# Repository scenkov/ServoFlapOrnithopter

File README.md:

# ESP32 board and SBUS receiver 
Thanks to K.Kakuta for the enormous work

Arduino CODE for ServoFlapOrnithopter [ServoFlapOrnithopter 2 servo by K.Kakuta](http://kakutaclinic.life.coocan.jp/SFOsys2S.html)

The library uses [ESP32Servo](https://www.arduino.cc/reference/en/libraries/esp32servo/) Allows ESP32 boards to control servo, tone and analogWrite motors using Arduino semantics.
This library can control a many types of servos. It makes use of the ESP32 PWM timers: the library can control up to 16 servos on individual channels No attempt has been made to support multiple servos per channel. 

### Installation
Download the contents of this repository on your computer. Open with PlatformIO

## Usage

Schematic 

Board 

New Servo Flap System by K.Kakuta

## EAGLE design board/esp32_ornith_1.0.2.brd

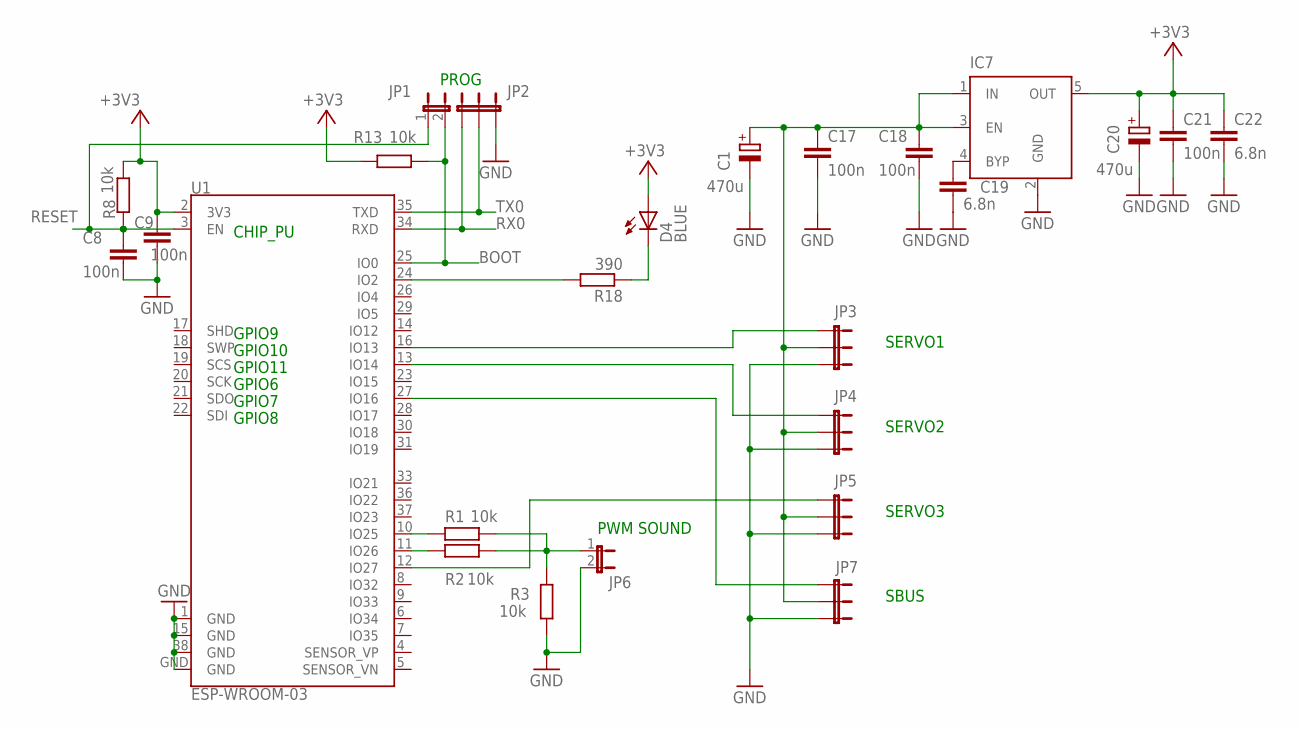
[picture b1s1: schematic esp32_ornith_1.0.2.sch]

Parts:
C1, C20: 470u; SMC_D
C8, C9: 100n; C0603
C17, C18, C21: 100n; C0603K
C19, C22: 6.8n; C0603K
D4: BLUE; LED-0603
IC7: MIC5219XX; SOT23-5
JP1, JP6: JUMPER-2PTH; 1X02
JP2, JP3, JP4, JP5, JP7: JUMPER-3PTH; 1X03
R1, R2, R3, R8, R13: 10k; R0603
R18: 390; R0603
U1: ESP-WROOM-03

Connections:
+3V3: C9.1, C20.+, C21.1, C22.1, D4.A, IC7.5 (OUT), R8.1, R13.2, U1.2 (3V3)
+4,2V: C1.+, C17.1, C18.1, IC7.1 (IN), IC7.3 (EN), JP3.2, JP4.2, JP5.2, JP7.2
BOOT: JP1.2, R13.1, U1.25 (IO0)
GND: C1.-, C8.2, C9.2, C17.2, C18.2, C19.2, C20.-, C21.2, C22.2, IC7.2 (GND), JP2.3, JP3.1, JP4.1, JP5.1, JP6.2, JP7.3, R3.1, U1.1 (GND), U1.15 (GND), U1.38 (GND), U1.GND
LED: R18.2, U1.24 (IO2)
unnamed: JP3.3, U1.16 (IO13)
unnamed: JP7.1, U1.27 (IO16)
unnamed: JP6.1, R1.2, R2.2, R3.2
unnamed: R1.1, U1.10 (IO25)
unnamed: R2.1, U1.11 (IO26)
unnamed: D4.C, R18.1
unnamed: JP4.3, U1.13 (IO14)
unnamed: JP5.3, U1.12 (IO27)
unnamed: C19.1, IC7.4 (BYP)
RESET: C8.1, JP1.1, R8.2, U1.3 (EN)
RX0: JP2.1, U1.34 (RXD)
TX0: JP2.2, U1.35 (TXD)

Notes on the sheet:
GPIO8
GPIO7
GPIO6
GPIO11
GPIO10
GPIO9
CHIP_PU
PROG
SBUS
SERVO1
SERVO2
SERVO3
PWM SOUND

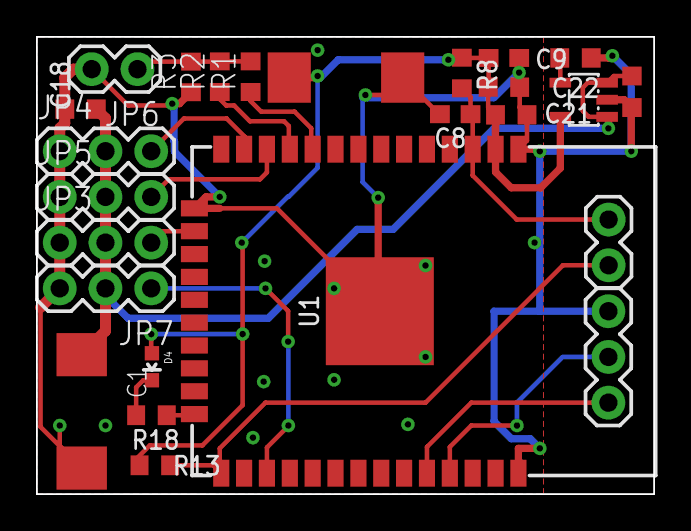
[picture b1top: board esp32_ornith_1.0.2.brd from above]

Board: 2 copper layers, 34.3 x 25.4 mm, 25 parts (0 on the bottom side), 17 nets.

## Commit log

2024-04-26 added media picture
2024-04-26 fixed style
2024-04-27 added schematic

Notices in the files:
parts and their libraries:
SparkFun-Passives: Licensing: Creative Commons ShareAlike 4.0 International - https://creativecommons.org/licenses/by-sa/4.0
